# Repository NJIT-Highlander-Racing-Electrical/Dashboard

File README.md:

# 2024-2025 Dashboard

A dashboard for the vehicle including data from:
* CVT
* BajaDAS
* Wheel Speed Sensors

## 2024-2025 Design Goals

There are many aspects to improve on from last year's dashboard, as well as several other new features we would like to add. Here are some topics to look into:

* Sunshade
  * Last year, the LCDs were too dim in direct sunlight. This year, we will be implementing a sunshade to fix this
  * This sunshade can be made out of sheet metal, formed to shape with a 3D printed mold, attached via screws to the dashboard's back cover, and painted black to minimize reflections.
 * Improved front cover
     * The acrylic is subject to cracking under pressure from the mounting screws
     * This year, we will be using polycarbonate and we can use rubber washers on the mounting screws too
 * Waterproofing
     * Last year, the dashboard was not waterproof. This year, we are adding gasket material
          * For the front, we will sandwich it between the polycarbonate and 3D printed frame
          * For the rear, we can put it between the rear 3D printed cover and the main 3D printed frame
* Integration of wheel speed sensor data
     * Wheel speed data can be used to determine whether a wheel has locked up or has wheelspin.
     * This should be a bright color that takes priority over anything else on the dashboard. For example, if the front left wheel is locked, the top of the left circular display should flash red.
* Brighter Displays
     * With the dark mode background last year, the displays were not bright enough. This year we are using light backgrounds.
* Driver Input
     * This year, we are implementing two push buttons on the back of the dashboard that the driver can use
     * One button will enable/diasble data logging
     * The other button will start/stop a stopwatch
     * Pressing both buttons will send a flag bit to DAS and flash the screen
          * Acts as a data marker for certain things
          * Like a vehicle data "screenshot"
* Other limitations/setbacks are discussed in the [2023-2024 Archive README](https://github.com/NJIT-Highlander-Racing-Electrical/Dashboard/tree/main/2023-2024%20Archive)

## 2024-2025 Known Issues

### GC9A01 SCLK Pin

The SPI Clock pin on the ESP32 is 18, but the PCB has it tied to 19. On the final version, we can just snip off the two pins that go into the PCB and swap them around with two small jumpers. Software Serial is not ideal for speed and would require software modifications.

### TLC5917 Chip 3 OE and R-EXT Pins

On the TLC5917 that controls the green fuel LEDs, the R-EXT pin is tied to ground. This causes the TLC to try to push infinite current into the LEDs. We can simply not solder that pin to the pad, and instead bend it up and jump it to a GND pin using the proper resistor.

The OE pin has the resistor that should have been attached to the R-EXT pin. The OE pin needs to be pulled LOW to enable the displays, so we can simply short the resistor there to ground.

Update: It appears that the green LEDs at their fixed brightness (lack of functional OE pin) are way too bright. I am modifying the resistor value to 47000k, which is far less blinding

### Fuel LEDs

 The leftmost red LED does not light up in the boot animation

## Hardware

* ESP32 Microcontroller (Select NodeMCU-32S board in Arduino IDE)
* TJA1051T CAN Transceiver
* 1" Seven Segment Displays (Kingbright SA10-21SRWA)
* 1.28" Round LCDs
* 5mm LEDs
* TLC5917 8-Channel Sinking Constant Current LED Drivers

## Key Features

1. Real-Time Vehicle Speed Display
2. Analog Dial and Digital Output of CVT RPM
4. Digital CVT Ratio
5. Current Time (HH:MM:SS)
6. LED Indicators for Fuel Level
7. Status LEDs for CVT Temperature, Data Acquisition, Battery Level, and Power On/off
8. CAN-BUS Communication with Rest of Vehicle
9. Boot screen including Highlander Racing logo

## ESP32 Dual-Core Utilization

* We decided to run CAN-Bus scanning solely on Core 0 (via a task) to ensure all messages are properly received
* Writing to displays, 7-segment drivers, and math functions all take time, which means messages can be missed

## Visuals

* Includes a custom boot animation featuring the Highlander Racing logo and Lightning McQueen's number: 95
* RPM Visual comes from this repository: https://github.com/VolosR/TDisplayDashboard/tree/main
* At the competition, it was apparent that the whole dash was fairly dim in the bright sun
  * Goals for next year should be to incorporate an (ideally detachable) sunshade, brighter LEDs, brighter LCD displays or a suitable alternative
  * Other nice-to-haves would be a pot for brightness control and/or some other kind of driver input to change menus or settings
  * G-Force on driver indicator with magnitude and direction would be neat as well

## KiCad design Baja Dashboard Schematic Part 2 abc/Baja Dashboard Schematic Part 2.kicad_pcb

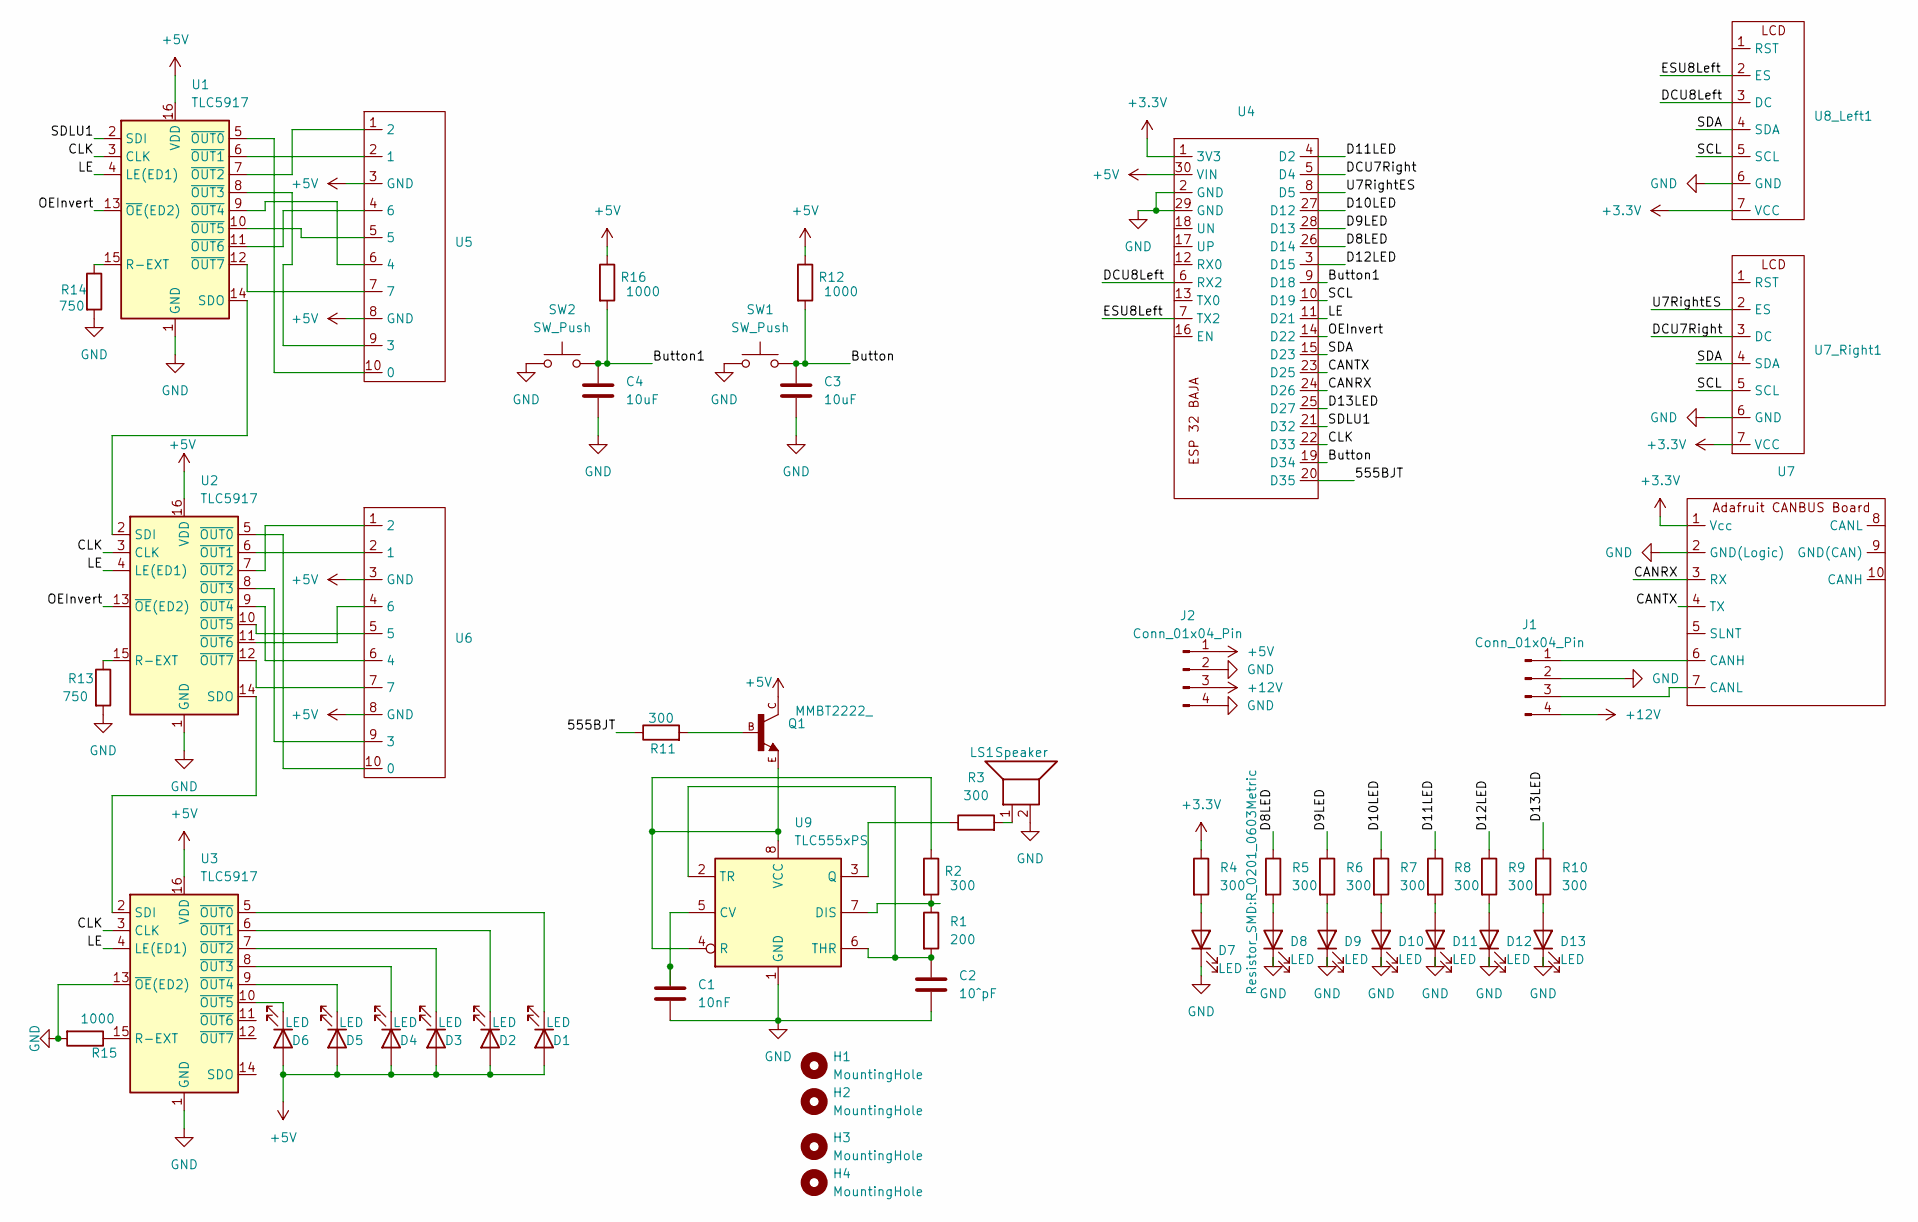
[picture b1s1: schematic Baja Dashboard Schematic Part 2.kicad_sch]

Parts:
C1: 10nF; CP_EIA-1608-08_AVX-J
C2: 10^pF; CP_EIA-1608-08_AVX-J
C3, C4: 10uF; CP_EIA-1608-08_AVX-J
D1, D2, D3, D4, D5, D6, D7, D8, D9, D10, D11, D12, D13: LED; LED 5mm Vertical
H1, H2, H3, H4: MountingHole; MountingHole_4.3mm_M4
J1: Conn_01x04_Pin
J2: Conn_01x04_Pin; PowerBoard
LS1: Speaker; Buzzer_12x9.5RM7.6
Q1: MMBT2222_; MMBT2222
R1: 200; R_0201_0603Metric
R2, R3, R4, R5, R6, R7, R8, R9, R10, R11: 300; R_0201_0603Metric
R12, R15, R16: 1000; R_0201_0603Metric
R13, R14: 750; R_0201_0603Metric
SW1, SW2: SW_Push; JST2pin
U1, U2, U3: TLC5917; TLC5917ID
U4: ESP 32 BAJA
U5, U6: baja 7 segment
U7, U7_Right1, U8_Left1: 1x7 Connectors
U9: TLC555xPS; TLC555

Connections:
+3.3V: R4.1, U4.1 (3V3), U7.1 (Vcc), U7_Right1.7 (VCC), U8_Left1.7 (VCC)
+5V: D1.2 (A), D2.2 (A), D3.2 (A), D4.2 (A), D5.2 (A), D6.2 (A), J2.1, Q1.C, R12.1, R16.1, U1.16 (VDD), U2.16 (VDD), U3.16 (VDD), U4.30 (VIN), U5.3 (GND), U5.8 (GND), U6.3 (GND), U6.8 (GND)
+12V: J1.4, J2.3
/555BJT: R11.1, U4.20 (D35)
/Button: C3.2, R12.2, SW1.2, U4.19 (D34)
/Button1: C4.2, R16.2, SW2.2, U4.9 (D18)
/CANRX: U4.24 (D26), U7.3 (RX)
/CANTX: U4.23 (D25), U7.4 (TX)
/CLK: U1.3 (CLK), U2.3 (CLK), U3.3 (CLK), U4.22 (D33)
/D8LED: R5.1, U4.26 (D14)
/D9LED: R6.1, U4.28 (D13)
/D10LED: R7.1, U4.27 (D12)
/D11LED: R8.1, U4.4 (D2)
/D12LED: R9.1, U4.3 (D15)
/D13LED: R10.1, U4.25 (D27)
/DCU7Right: U4.5 (D4), U7_Right1.3 (DC)
/DCU8Left: U4.6 (RX2), U8_Left1.3 (DC)
/ESU8Left: U4.7 (TX2), U8_Left1.2 (ES)
/LE: U1.4 (LE(ED1)), U2.4 (LE(ED1)), U3.4 (LE(ED1)), U4.11 (D21)
/OEInvert: U1.13 (~OE(ED2)), U2.13 (~OE(ED2)), U4.14 (D22)
/SCL: U4.10 (D19), U7_Right1.5 (SCL), U8_Left1.5 (SCL)
/SDA: U4.15 (D23), U7_Right1.4 (SDA), U8_Left1.4 (SDA)
/SDLU1: U1.2 (SDI), U4.21 (D32)
/U7RightES: U4.8 (D5), U7_Right1.2 (ES)
GND: C1.2, C2.2, C3.1, C4.1, D7.1 (K), D8.1 (K), D9.1 (K), D10.1 (K), D11.1 (K), D12.1 (K), D13.1 (K), J1.2, J2.2, J2.4, LS1.2, R13.2, R14.2, R15.2, SW1.1, SW2.1, U1.1 (GND), U2.1 (GND), U3.1 (GND), U3.13 (~OE(ED2)), U4.2 (GND), U4.29 (GND), U7.2 (GND(Logic)), U7_Right1.6 (GND), U8_Left1.6 (GND), U9.1 (GND)
unnamed: D1.1 (K), U3.5 (~OUT0)
unnamed: D2.1 (K), U3.6 (~OUT1)
unnamed: D3.1 (K), U3.7 (~OUT2)
unnamed: D4.1 (K), U3.8 (~OUT3)
unnamed: D5.1 (K), U3.9 (~OUT4)
unnamed: D6.1 (K), U3.10 (~OUT5)
unnamed: D7.2 (A), R4.2
unnamed: D8.2 (A), R5.2
unnamed: D9.2 (A), R6.2
unnamed: D10.2 (A), R7.2
unnamed: D11.2 (A), R8.2
unnamed: D12.2 (A), R9.2
unnamed: D13.2 (A), R10.2
unnamed: J1.1, U7.6 (CANH)
unnamed: J1.3, U7.7 (CANL)
unnamed: LS1.1, R3.2
unnamed: Q1.B, R11.2
unnamed: R14.1, U1.15 (R-EXT)
unnamed: U1.14 (SDO), U2.2 (SDI)
unnamed: U1.5 (~OUT0), U5.10 (0)
unnamed: U1.6 (~OUT1), U5.2 (1)
unnamed: U1.7 (~OUT2), U5.1 (2)
unnamed: U1.8 (~OUT3), U5.9 (3)
unnamed: U1.9 (~OUT4), U5.6 (4)
unnamed: U1.10 (~OUT5), U5.5
unnamed: U1.11 (~OUT6), U5.4 (6)
unnamed: U1.12 (~OUT7), U5.7
unnamed: R13.1, U2.15 (R-EXT)
unnamed: U2.14 (SDO), U3.2 (SDI)
unnamed: U2.5 (~OUT0), U6.10 (0)
unnamed: U2.6 (~OUT1), U6.2 (1)
unnamed: U2.7 (~OUT2), U6.1 (2)
unnamed: U2.8 (~OUT3), U6.9 (3)
unnamed: U2.9 (~OUT4), U6.6 (4)
unnamed: U2.10 (~OUT5), U6.5
unnamed: U2.11 (~OUT6), U6.4 (6)
unnamed: U2.12 (~OUT7), U6.7
unnamed: R15.1, U3.15 (R-EXT)
unnamed: C1.1, U9.5 (CV)
unnamed: R1.1, R2.2, U9.7 (DIS)
unnamed: R3.1, U9.3 (Q)
unnamed: Q1.E, R2.1, U9.4 (R), U9.8 (VCC)
unnamed: C2.1, R1.2, U9.2 (TR), U9.6 (THR)

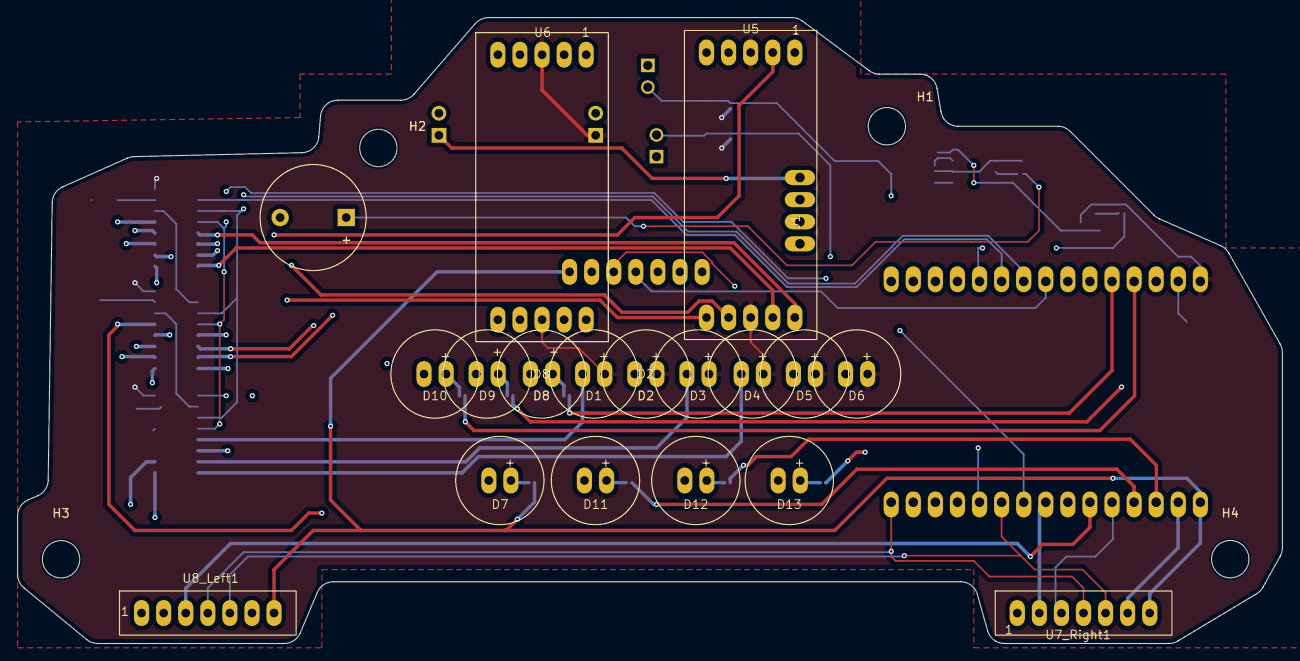
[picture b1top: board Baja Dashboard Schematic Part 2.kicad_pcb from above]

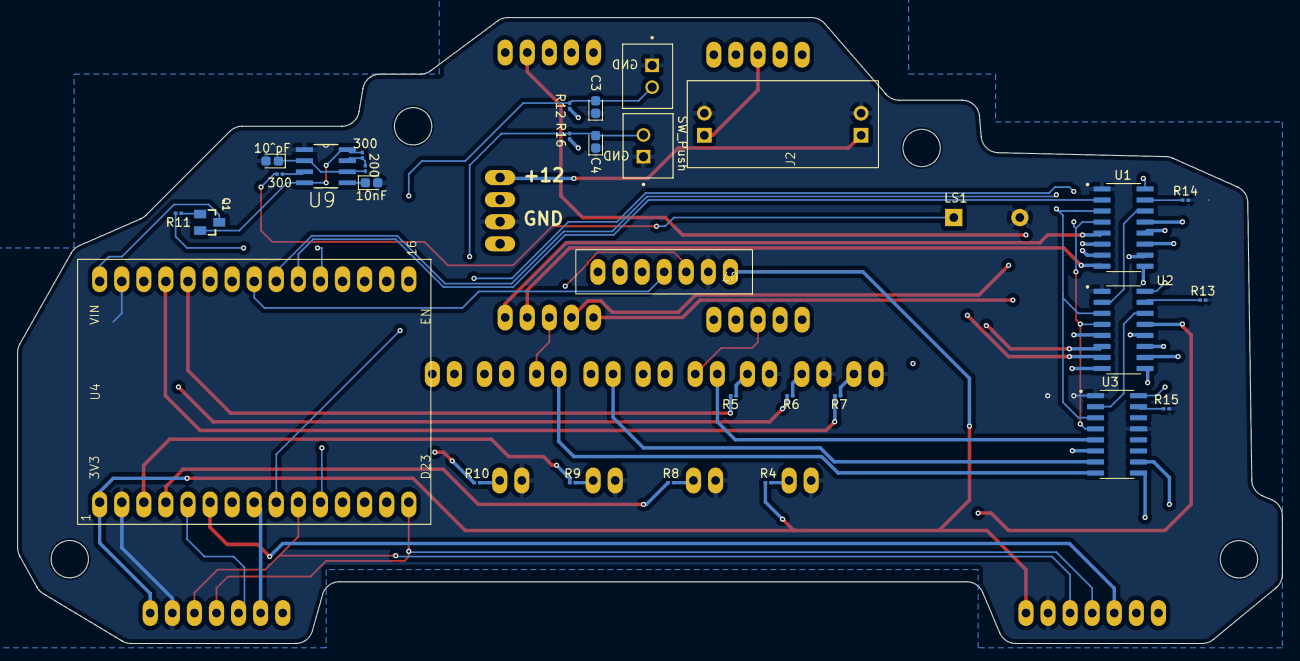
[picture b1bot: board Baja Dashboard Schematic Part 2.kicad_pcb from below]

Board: 4 copper layers, 145.5 x 72.0 mm, 53 parts (30 on the bottom side), 68 nets.

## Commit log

2023-09-30 Create CAD-Model
2023-11-18 Rename dial.h to 2023_Dashboard/dial.h
2023-11-18 Add files via upload
    11/18/23 V3
2024-03-13 Rename Dashboard v37.step to 3D Models/Dashboard v37.step
2024-03-13 Rename image.png to Dasjhboard_Concept.png
2024-03-13 Rename Dasjhboard_Concept.png to Dashboard_Concept.png
2024-03-17 Rename 2023_Dashboard/NotoSansBold36.h to Software/Archive/NotoSansBold36.h
2024-03-17 Create file
2024-03-17 Rename 2023_Dashboard/2023_Dashboard.ino to Software/Archive/2023_Dashboard.ino
2024-03-17 Rename 2023_Dashboard/GIFDraw.ino to Software/Archive/GIFDraw.ino
2024-03-17 Rename 2023_Dashboard/data/cargif.gif to Software/Archive/Data/cargif.gif
2024-03-17 Rename 2023_Dashboard/data/dial.jpg to Software/Archive/data/dial.jpg
2024-03-17 FolderChange
2024-03-17 Rename 2024_Dashboard.ino to DashboardSoftware.ino
2024-03-18 Rename DashboardSoftware/RPM_Dial_Image.h to DashboardSoftware/Archive/RPM_Dial_Image.h
2024-04-10 Create KiCAD
2024-04-10 this is hte second one
2024-04-21 reorganized all fines on desktop version
2024-04-21 Rename IMG_0789.JPEG to Photos/IMG_0789.JPEG
2024-04-21 Rename Dashboard_Concept.png to Photos/Dashboard_Concept.png
2024-05-14 moving 2023-2024 files to archive
2024-05-14 adding default files and folders
2024-09-24 Add visual demo program
2024-09-24 Add additional research topics
2024-09-25 Fix issue where TFT_CS not properly defined in User_Setup.h
2024-09-25 Minor display updates
2024-09-29 Add libraries message
2024-09-29 Update libraries message
2024-10-18 Create Library123
2024-10-20 Update Software Folder Layout
2024-10-20 Update 23-24 Code For 24-25 Dash
    Note there is an issue with the TFT_eSPI library that prevents this program from compiling
2024-11-14 Remove dummy file
2024-11-19 Rename Dashboard2025 v19.f3z to Dashboard2025 v19.f3z
2024-11-19 Rename Dashboard2025 v19.step to Dashboard2025 v19.step
2024-11-20 Rename PCB2024.zip to PCB/PCB2024.zip
2024-11-23 Move to 3D models folder
2024-11-24 Reupload file that got corrupted from folder move
2024-11-24 Update Documentation
2024-12-04 New version with filleted edges
2024-12-05 Move previous versions to dedicated folder
2024-12-07 Add new GBR/DRL Files, Add new part position files
2024-12-15 Remove all Blind/Buried Vias for PCB manufacturing
2024-12-15 Fix top layer to bottom layers in component sheet
2024-12-18 Fix blind/buried via on LE trace
2025-01-06 Update 3D Model
2025-02-06 Update GBR_AND_DRL_Files.zip
    not sure why this isnt updated
2025-02-06 Attempt to move libraries to project folder
    I spent lots of time trying to incorporate all of these libraries into a single project folder, but Arduino doesn't like this. Since most of the libraries are written with references to files like th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
2025-02-06 Move back to regular arduino library folder
2025-02-12 Revert back to Arduino IDE libraries
    Everything now uses libraries stored in Arduino/libraries folder. Code was updated to use variables stored in BajaCAN.h, still have to check if there are other variables that are redefined and need t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
2025-02-12 Add libraries
    These are copied from my Documents/Arduino/libraries folder on my laptop, from which I got a successful upload using V2.0.17 ESP32 in board manager. Not sure if everything is exactly correct, as the 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
2025-02-12 ???
    This should have been uploaded with my previous commit regarding using Documents/Arduino/libraries, not sure why it didnt complete
2025-02-12 Update 5mm LED GPIO pin values for new PCB
2025-02-12 Update 5mm LED Pin numbers again; PCB pin names are inconsistent with ESP32 GPIO
2025-02-12 Fix D8 and D2 silkscreen on wrong layer
2025-02-12 Remove debug print statement and decrease 7-segment brightness for testing
2025-02-12 Nothing eventful
2025-02-15 Most recent up to date everything compiling code
2025-02-20 fixed PCB
    Fixed pin 15 issue
2025-02-20 Changes to UI
    White background
    black text
    timer is set to 04:55:55 as a test, comment it out and uncomment the main function code
2025-03-02 Updated screen options
    Changed from calculated speed for mph to gpsvelocity
    Implemented gpsvelocity for wheel traction and locked wheel indicator lights
    implemented brightness control
    implemented data marker
    Started error code screen
2025-03-08 Finished implementing button controls
    Vomited if statements. Screw you, I'm not optimizing the code. Nothing mechanical is dependent on electrical systems.
2025-03-12 Remove outdate code from main folder of repo
2025-03-29 Restore README
2025-03-29 Added elapsed time and made fixes
2025-03-29 Update to latest BajaCAN.h driver
2025-03-29 Ignore
2025-03-29 See Changelog
    Renamed all fuel related variables to ledBar or batteryLevel or just Led for clarity
    Added comments to various functions
    Removed unused code for calculating vehicle speed from CVT secondary RPM (using GPS Velocity)
    Cleaned up loop() function
    Fixed spelling
    Modified variable names to be consistent with camelCase
2025-03-29 See Changelog
    Revised variable names for clarity
    Move most code in loop() into individual functions
    Add more comments
    Remove unused code (2WD/4WD switch, etc)
2025-03-29 More updates. Just see the difsf
2025-03-29 More updates
2025-03-30 Push display program
2025-03-31 Add "Screenshot" functionality and status health bit integration
2025-04-01 Major Updates
    Add more comments
    Update wheelspin/skid code to use data sent from Wheel Speed sensors instead of calculating its own
    Categorize code before setup()
    Remove unused variables
    Convert all serial prints to debug prints
2025-04-01 Update both programs to use lower color depth on right display
    I believe the color depth was defaulting to 16 bit, which meant that the ESP32 could not handle full screen rendering. It was limited to roughly 235x235, so there were weird cutoffs to the round disp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
2025-04-01 Update Display Demo program to use black backgrounds; easier on ye old eyes
2025-04-01 Experimenting with Adafruit Canvas Updating
    Stopwatch with milliseconds caused severe display flicker. Using their Canvas function, you can generate a whole bitmap and push that to the display at once to eliminate flicker. Only downside is not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
2025-04-01 Fix position of stopwatch
2025-04-01 Nothing important
2025-04-02 Update to lates CAN Driver
2025-04-02 Fix half baud rate
2025-04-02 Updated to latest CAN
2025-04-02 Fix Syntax Errors
2025-04-12 Fixed the RPM gauge and buttons
2025-04-12 fixed clock
2025-04-13 Fix DAQ Led not resetting, Fix RPM dial position
2025-04-13 Fix bug where red fuel led would not light
    This happened because TFT_eSPI was somehow latching onto pin 12 and making it something other than an output. This was after we had declared it as an output earlier in the code, so when we go to use 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
2025-04-13 Fix sd logging/stopwatch/screenshot button presses and fix battery led flicker
2025-04-17 MInor updates to display version program
2025-04-19 Update 3D models
2025-05-02 Add dashboard odometer to trip (stopwatch) mode
2025-05-03 Update to latest CAN, start using lowest wheel speed for vehicle speed
2025-05-03 Update odometer
2025-05-03 I think this fixed the CAN not working issue
2025-05-03 Fix LED bar not working
2025-05-03 Test update since CAN still not working
2025-05-04 Latest Code, was working with PCAN, ensured that termination resistor was active
2025-05-04 Fix odometer positioning
2025-05-04 Make screenshot actually flash both screens
2025-05-04 Remove status bit stuff
2025-05-04 Remove wheel spin skid screens, werent working properly
2025-05-10 Attempt to fix dashboard CAN not working issue
    Only works when code is uploaded from laptop
    When booted on without laptop, does not work
    still works when laptop unplugged after uploading code
2025-05-11 Revert back to 500kbps
2025-05-11 Fix bug where stopwatch was overwriting gps time
2025-05-11 Actually fixing bug from before
2025-05-11 finally fixed
2025-05-11 Remove packetID pritning
2025-06-13 Fix odometer and add delay for CAN initializatoin
2025-06-13 Use actual miles traveled calculations
2025-06-13 fix cvt ratio printing over for odometer, attempt to fix intermitten can startup
2025-06-13 Attempt to fix odometer creeping up over time even at 0 speed
2025-06-13 make sure no gps velocity results in odometer creep up
2025-06-13 Update odometer to use wheel speed for more accuracy
2025-06-14 Flip buttnons for better usability (more logical)
2025-09-06 Disable Debug
2025-09-07 Update to latest CAN
